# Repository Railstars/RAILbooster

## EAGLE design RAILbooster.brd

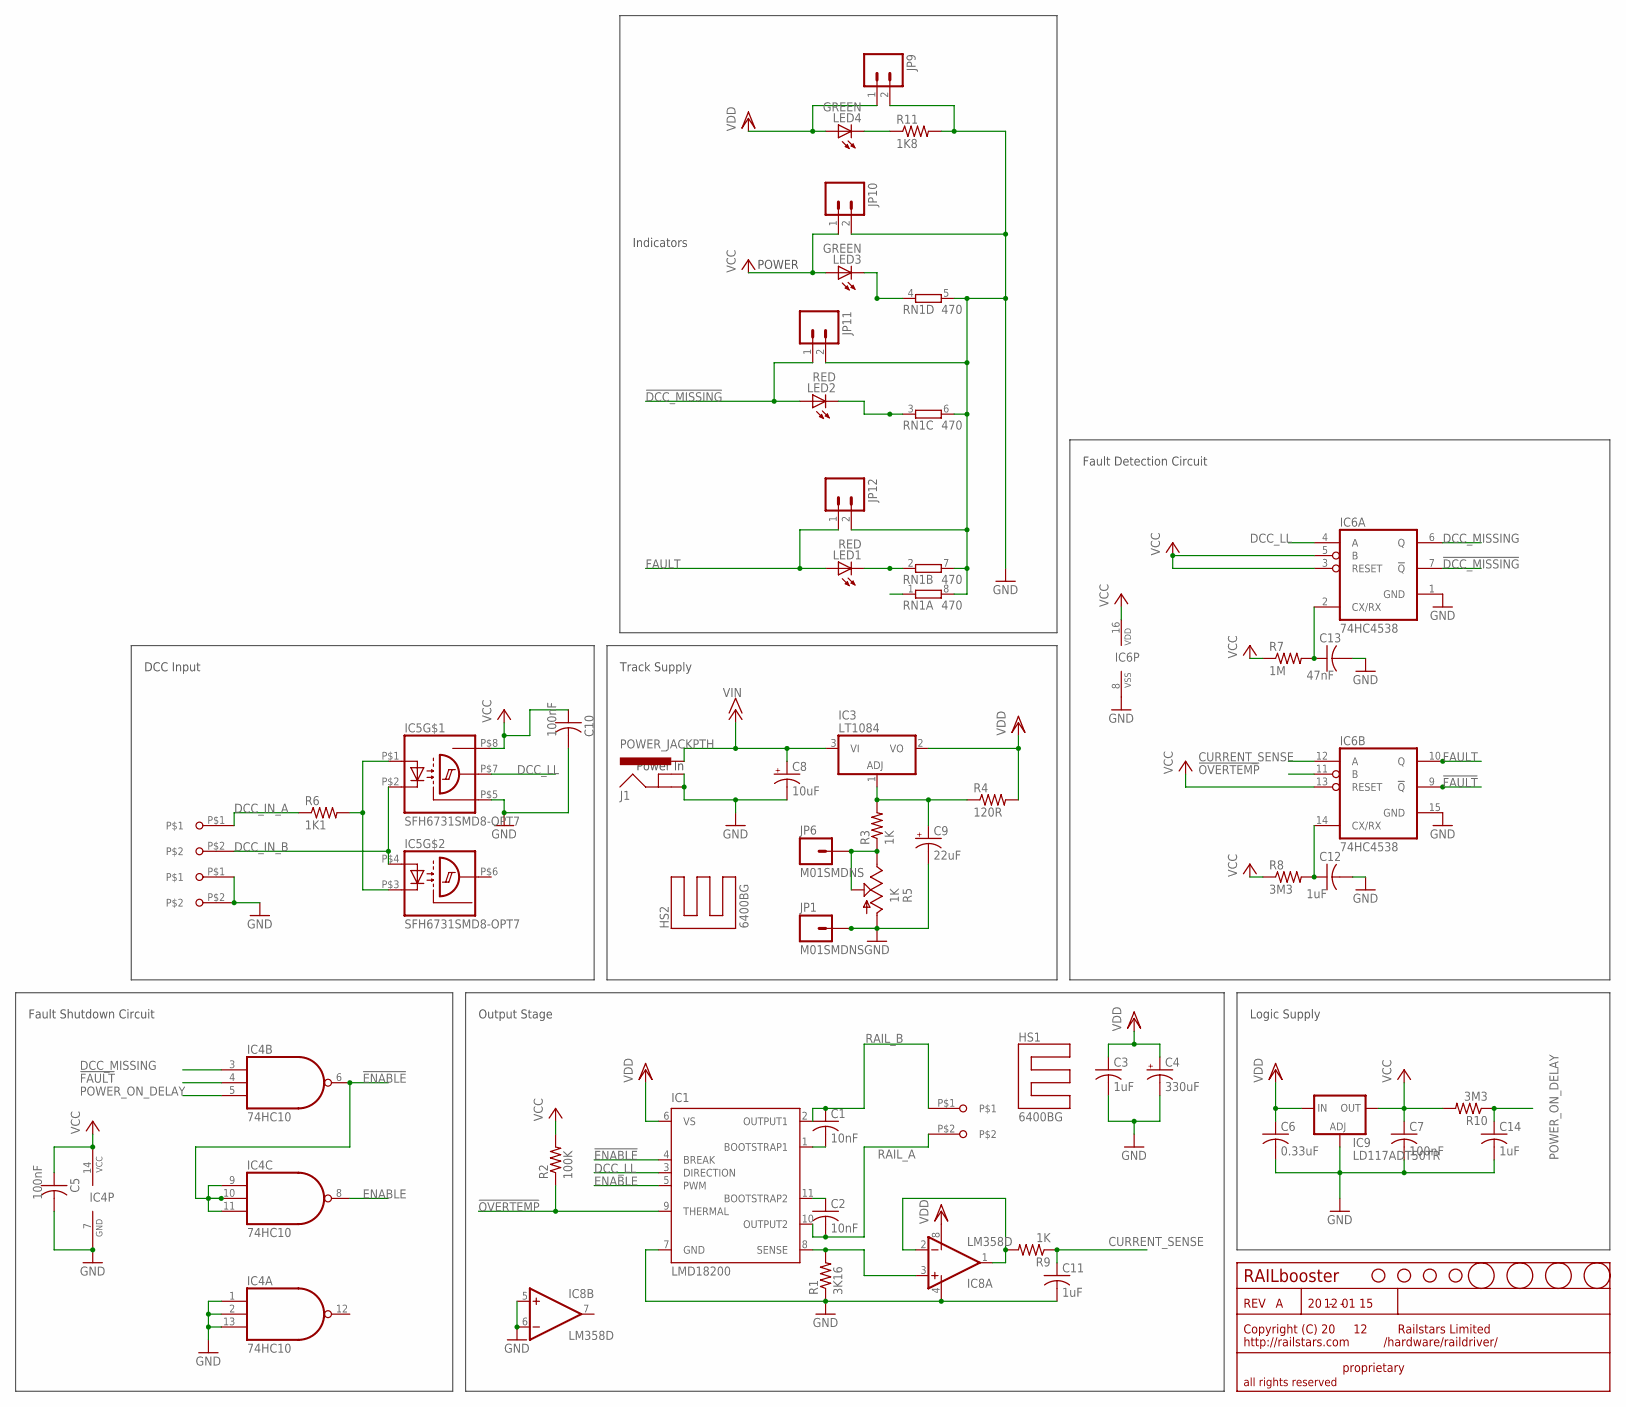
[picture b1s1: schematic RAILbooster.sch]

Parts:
C1, C2: 10nF; C0603
C3, C11, C12, C14: 1uF; C0603
C4: 330uF; E5-10,5
C5, C7, C10: 100nF; C0603
C6: 0.33uF; C0603
C8: 10uF; E2-5
C9: 22uF; E2-5
C13: 47nF; C0603
HS1, HS2: 6400BG
IC1: LMD18200; TO-220-11
IC3: LT1084; TO-220
IC4: 74HC10; SO14
IC5: SFH6731SMD8-OPT7; SMD8-OPT7
IC6: 74HC4538; SOIC-16
IC8: LM358D; SO08
IC9: LD117ADT50TR; DPACK
J1: POWER_JACKPTH; POWER_JACK_PTH
JP1, JP6: M01SMDNS; 1X01NS
JP2, JP3, JP4, JP5: STAND-OFF
JP9, JP10, JP11, JP12: M02PTH; 1X02
LED1, LED2: RED; LED-0603
LED3, LED4: GREEN; LED-0603
R1: 3K16; R0603
R2: 100K; R0603
R3, R9: 1K; R1206
R4: 120R; R0603
R5: 1K; S64W
R6: 1K1; R1206
R7: 1M; R0603
R8, R10: 3M3; R0603
R11: 1K8; R1206
RN1: 470; EXBS8V
U$1: RAILSTARS_LOGO20MM; RAILSTARS_1IN
U$5, U$6, U$7, U$8: FIDUCIAL; FIDUCIAL_1MM
X1, X3, X4: SCREWTERMINAL-5.08-2

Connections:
!DCC_MISSING: IC6.7 (!Q), JP11.1, LED2.A
!ENABLE: IC1.4 (BREAK), IC4.6 (O), IC4.9 (I0), IC4.10 (I1), IC4.11 (I2)
!FAULT: IC4.4 (I1), IC6.9 (!Q)
!OVERTEMP: IC1.9 (THERMAL), IC6.11 (B), R2.1
CURRENT_SENSE: C11.1, IC6.12 (A), R9.1
CURRENT_SENSE_UNBUFFERED: IC8.1 (OUT), IC8.2 (-IN), R9.2
CXRXA: C13.1, IC6.2 (CX/RX), R7.2
CXRXB: C12.1, IC6.14 (CX/RX), R8.2
DCC_IN_A: R6.1, X1.P$1
DCC_IN_B: IC5.P$2 (C), IC5.P$4 (A), X1.P$2
DCC_LL: IC1.3 (DIRECTION), IC5.P$7 (OUT), IC6.4 (A)
DCC_MISSING: IC4.3 (I0), IC6.6 (Q)
ENABLE: IC1.5 (PWM), IC4.8 (O)
FAULT: IC6.10 (Q), JP12.1, LED1.A
GND: C3.2, C4.-, C5.2, C6.2, C7.2, C8.-, C9.-, C10.2, C11.2, C12.2, C13.2, C14.2, IC1.7 (GND), IC4.1 (I0), IC4.2 (I1), IC4.7 (GND), IC4.13 (I2), IC5.P$5 (GND), IC6.1 (GND), IC6.8 (VSS), IC6.15 (GND), IC8.4 (V-), IC8.5 (+IN), IC8.6 (-IN), IC9.1 (ADJ), J1.GND, J1.GNDBREAK, JP1.1, JP9.2, JP10.2, JP11.2, JP12.2, R1.1, R5.A, R11.2, RN1.5 (2), RN1.6 (2), RN1.7 (2), RN1.8 (2), X3.P$1, X3.P$2
unnamed: JP6.1, R3.1, R5.E, R5.S
unnamed: C1.2, IC1.1 (BOOTSTRAP1)
unnamed: C2.1, IC1.11 (BOOTSTRAP2)
unnamed: IC1.8 (SENSE), IC8.3 (+IN), R1.2
unnamed: LED3.C, RN1.4 (1)
unnamed: C9.+, IC3.1 (ADJ), R3.2, R4.1
unnamed: IC5.P$1 (A), IC5.P$3 (C), R6.2
unnamed: LED2.C, RN1.3 (1)
unnamed: LED1.C, RN1.2 (1)
unnamed: LED4.C, R11.1
POWER_ON_DELAY: C14.1, IC4.5 (I2), R10.1
RAIL_A: C2.2, IC1.10 (OUTPUT2), X4.P$2
RAIL_B: C1.1, IC1.2 (OUTPUT1), X4.P$1
VCC: C5.1, C7.1, C10.1, IC4.14 (VCC), IC5.P$8 (VCC), IC6.3 (RESET), IC6.5 (B), IC6.13 (RESET), IC6.16 (VDD), IC9.4 (OUT), JP10.1, LED3.A, R2.2, R7.1, R8.1, R10.2
VDD: C3.1, C4.+, C6.1, IC1.6 (VS), IC3.2 (VO), IC8.8 (V+), IC9.3 (IN), JP9.1, LED4.A, R4.2
VIN: C8.+, IC3.3 (VI), J1.PWR

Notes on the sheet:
Track Supply
Logic Supply
RAILbooster
12 01 15
Power In
Indicators
DCC Input
Fault Shutdown Circuit
Fault Detection Circuit
Output Stage
POWER
proprietary
/hardware/raildriver/
all rights reserved

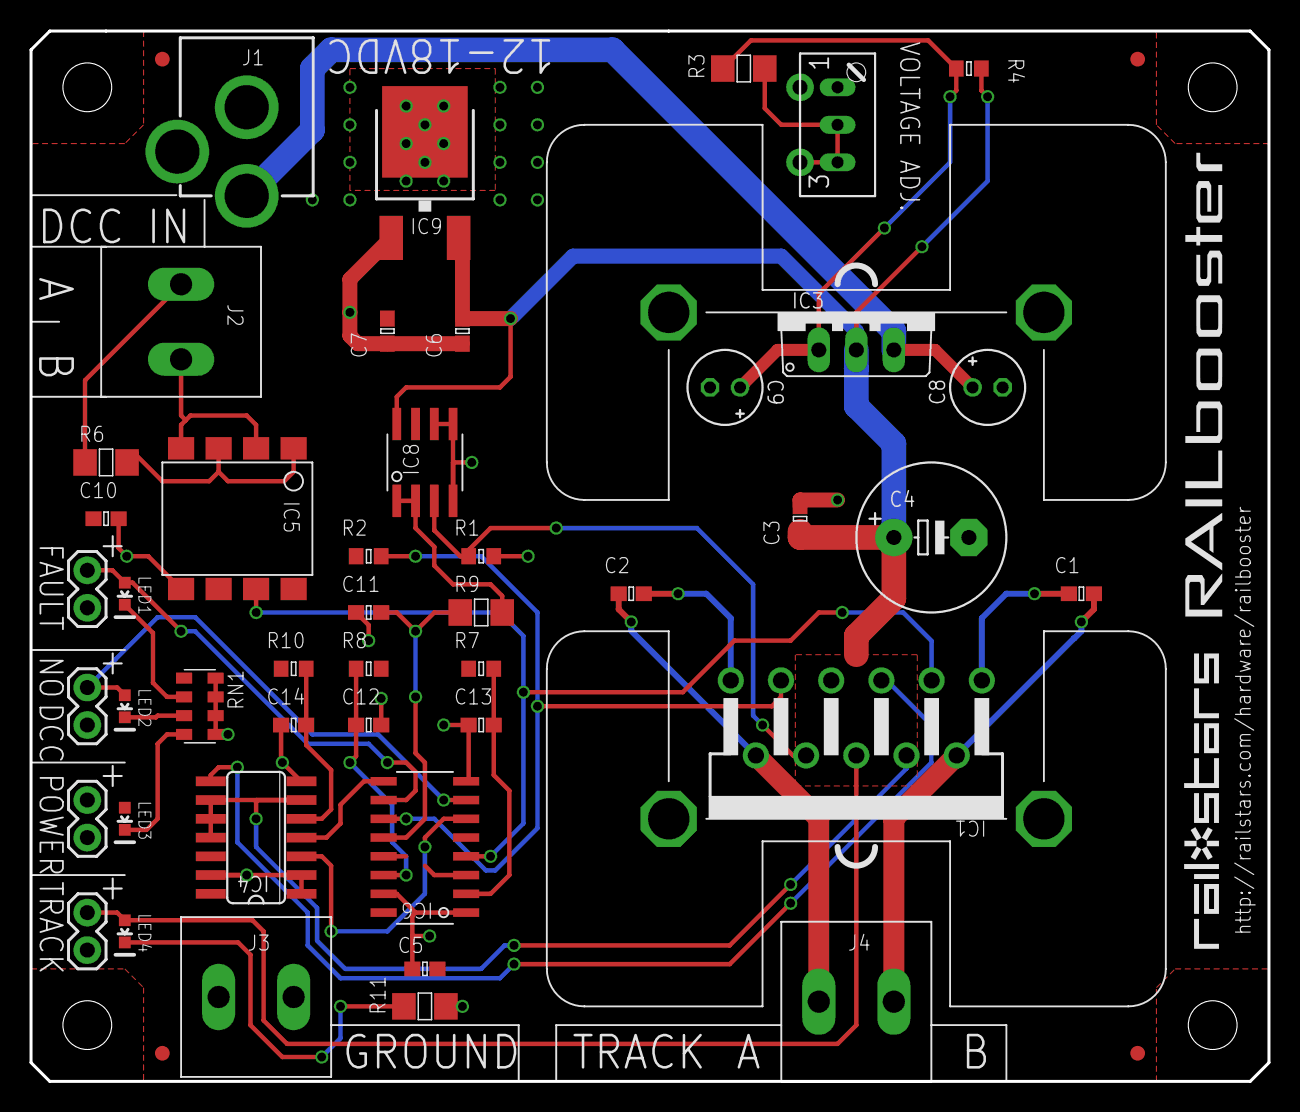
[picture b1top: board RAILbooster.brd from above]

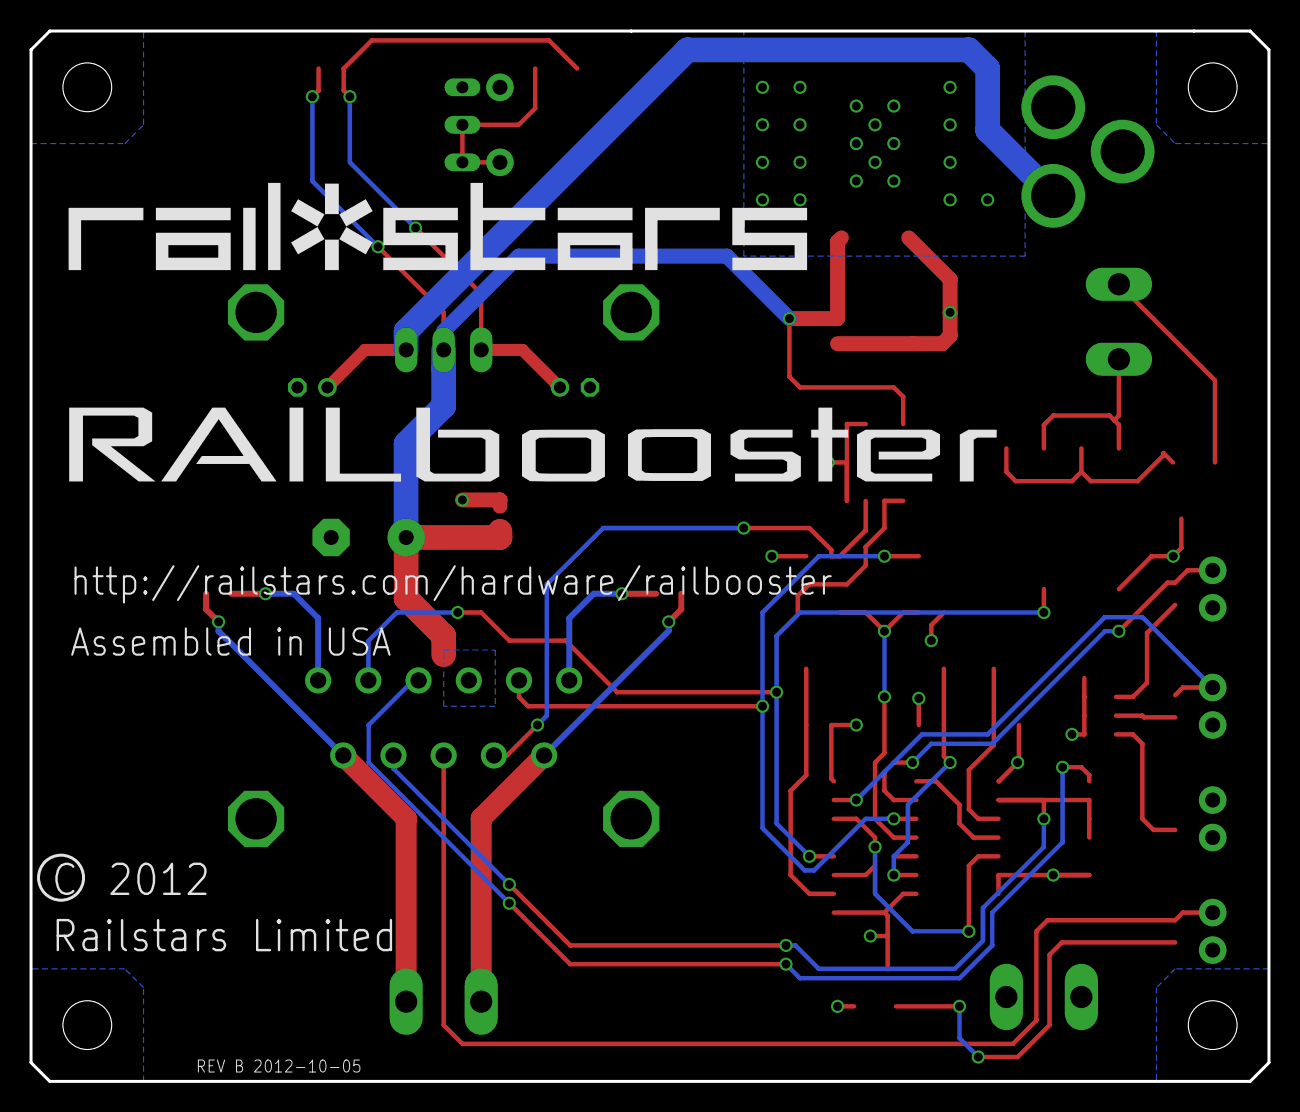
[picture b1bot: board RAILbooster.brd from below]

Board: 2 copper layers, 83.8 x 71.1 mm, 61 parts (2 on the bottom side), 31 nets.

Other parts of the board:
U$2: LOGO_RAILBOOSTER_5MM
U$3: LOGO_RAILBOOSTER_2.5MM
U$4: RAILSTARS_50MM

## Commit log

2010-08-20 LOLbooster Output Stage 20100810
2010-08-20 LOLbooster Output Stage 20100819
2010-08-25 LOLbooster Power Supply 20100821
2010-09-01 LOLbooster Power Supply 20100901
2010-10-09 LOLbooster Input Stage 20100912
2010-10-27 LOLbooster 20101009
2010-10-29 LOLbooster 20101028
2010-11-08 LOLbooster 20101029
2010-11-29 LOLbooster REV A
2011-04-27 LOLbooster REV B
2012-02-17 RAILbooster-2012-01-15
2012-10-09 RAILbooster-2012-10-05
2014-12-14 Railbooster 20121005 Final

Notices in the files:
parts and their libraries:
SparkFun-Connectors: Licensing: CC v3.0 Share-Alike You are welcome to use this library for commercial purposes.
Artificial Science: Copyright (C) 20
